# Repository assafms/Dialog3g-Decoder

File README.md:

# Arad Dialog 3G Water Meter Decoder

ESPHome custom component and PCB for reading Arad Dialog 3G water meters using an SI4432 (XL4432) RF module and an ESP8266/ESP32.

## Overview

The Arad Dialog 3G is a water meter deployed in Israel and other countries operating at 916.3 MHz (868 MHz in some regions). This project provides:

- **Custom PCB** connecting an XL4432 module to an ESP via SPI
- **ESPHome component** that receives and decodes meter packets
- **Unified LFSR validation** for all meter groups — single model, no per-group configuration
- **3-bit error correction** — recovers packets with up to 3 corrupted bits
- **ID recovery** — corrects corrupted meter IDs using per-meter constants from validated packets

## Meter Groups

| Group | Bytes 8-9 | Cons Divisor | Notes |
|-------|-----------|-------------|-------|
| Standard | `0x00 0x00` | ÷10 (0.1 m³) | Residential meters |
| Sonata/x40 | `0x00 0x40` | ÷1000 (1 liter) | Commercial/street meters |
| 3D0C | `0x3D 0x0C` | ÷10 (0.1 m³) | Older model |

All groups use the same unified LFSR model with a single universal offset (`0x6FF11521E8`). No per-group detection or configuration needed — bytes 8-9 are just more data bits in the LFSR.

## How It Works

The meter transmits a 21-byte FSK/Manchester-encoded packet every ~30 seconds containing the meter ID and consumption reading. The ESPHome component validates every packet using a unified LFSR-based GF(2) model that works for all meter groups. It also applies up to 3-bit error correction to recover packets with minor RF corruption. Only validated readings are published to Home Assistant.

## Hardware

| Component | Approximate Cost |
|-----------|-----------------|
| ESP8266 or ESP32 | ~$4 |
| XL4432 / SI4432 RF module | ~$2 |
| Custom PCB (see `PCB/`) or manual SPI wiring | ~$0.50 |

See `PCB/` for Eagle source files, Gerber outputs, and board photos.

## RF Parameters

| Parameter | Value |
|-----------|-------|
| Frequency | 916.3 MHz |
| Modulation | FSK |
| Encoding | Manchester (IEEE 802.3) |
| Data Rate | 59.45 kbps |
| Frequency Deviation | 175 kHz |
| Receiver Bandwidth | 600 kHz |
| Transmission Interval | ~30 seconds |
| Preamble | 7 nibbles |
| Sync Word | `0x3E 0x69` |
| Payload | 21 bytes, fixed length, no CRC |

## Quick Start

1. Build the PCB or wire the XL4432 to the ESP via SPI (see `esphome/README.md` for pinout)
2. Copy `esphome/custom_components/xl4432_spi_sensor/` to your ESPHome `custom_components/` directory
3. Add to your YAML:

```yaml
sensor:
  - platform: xl4432_spi_sensor
    name: water_meter
    cs_pin: GPIO15
    meter_id: "0x4E61BC"
    accuracy_decimals: 1
```

4. Find your meter ID: read the decimal serial number on the meter, convert to hex. Example: decimal `5136830` → hex `0x4E61BE`. The packet transmits this big-endian.

## Packet Sniffer Mode

To capture raw packets from all nearby meters:

```yaml
sensor:
  - platform: xl4432_spi_sensor
    name: sniffer
    cs_pin: GPIO15
    meter_id: "0x000000"
    packet_sniff: true
```

All received packets are logged at INFO level. No validation or filtering is performed.

## Wireless Connection

Add `tcp_server: true` to stream packets over WiFi to the Android collector app instead of USB:

```yaml
sensor:
  - platform: xl4432_spi_sensor
    name: sniffer
    cs_pin: GPIO15
    meter_id: "0x000000"
    packet_sniff: true
    tcp_server: true
```

Enable phone hotspot, configure ESPHome WiFi with the hotspot credentials, and the Android app auto-discovers the ESP on port 4321.

## Packet Structure

| Byte(s) | Field | Description |
|---------|-------|-------------|
| 0-1 | Header | Static (`0x0A 0xEC`) |
| 2-4 | Type | Meter type / firmware variant |
| 5-7 | Meter ID | 3 bytes, big-endian |
| 8-9 | Group | `0x00 0x00` standard, `0x00 0x40` x40, `0x3D 0x0C` 3D0C |
| 10-12 | Consumption | 3 bytes, little-endian. STD/3D0C: ÷10 for m³. Sonata/x40: ÷1000 for m³ |
| 13-14 | Status | Usually `0x00 0x05` |
| 15-19 | Scramble | GF(2) integrity field |
| 20 | Trailer | High nibble only (low nibble unreliable due to Manchester timing drift) |

## GF(2) Scrambling Algorithm

Bytes 15-19 of each packet contain a 40-bit value that is a **linear function over GF(2)** of all data bytes 0-14, computed via a single 40-bit LFSR:

```
scrambled = OFFSET ^ ⨁(LFSR_vec[pos] for each set bit in bytes 0-14)
```

Where:
- **OFFSET** = `0x6FF11521E8` — universal, same for all meter groups
- All 120 basis vectors are consecutive states of a 40-bit LFSR (seed `0x51AAF3D980`, 3 feedback taps)
- Forward chain: bytes 12→11→10→9→8→7→6→5→4→3→2→1→0 (104 states)
- Backward chain: bytes 13→14 (16 states, stored as lookup)
- **^** is bitwise XOR

### Validation

Single model for all groups: compute expected scramble via LFSR from bytes 0-14, compare to received bytes 15-19. Up to 3 corrupted bits can be automatically corrected using 160 syndrome bits (120 data + 40 scramble). Achieves 80% STD, 78% x40, 83% 3D0C validation rate. See `PROTOCOL.md` for full details and basis vector tables.

## Links

- [Dialog3g-Decoder-research](https://github.com/assafms/Dialog3g-Decoder-research) — Research repo with analysis scripts, Android collector app, and detailed protocol documentation
- [rtl_433 Protocol 260](https://github.com/merbanan/rtl_433) — SDR-based decoder
- [rtl_433 Issue #1992](https://github.com/merbanan/rtl_433/issues/1992) — Original protocol analysis
- [rtl_433 Discussion #3414](https://github.com/merbanan/rtl_433/discussions/3414) — Arad Sonata analysis

## License

This project is the result of independent reverse engineering for research and interoperability purposes. Not affiliated with Arad Ltd.

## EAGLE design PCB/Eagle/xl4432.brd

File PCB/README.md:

# PCB Design

Custom PCB connecting an XL4432 (SI4432) RF module to an ESP8266/ESP32 via SPI.

## Contents

| Directory | Description |
|-----------|-------------|
| `Eagle/` | Source schematic and board files (Eagle CAD) |
| `Gerber/` | Production-ready Gerber files (PCBWay compatible) |

## Assembly Notes

- **R1, R2, R3**: Use 0-ohm resistors or solder bridges (short the pads)
- See `schematic.png` and `pcb.png` for reference
- `completed board.png` shows an assembled example

## Bill of Materials

See `Eagle/BOM` for the full component list.

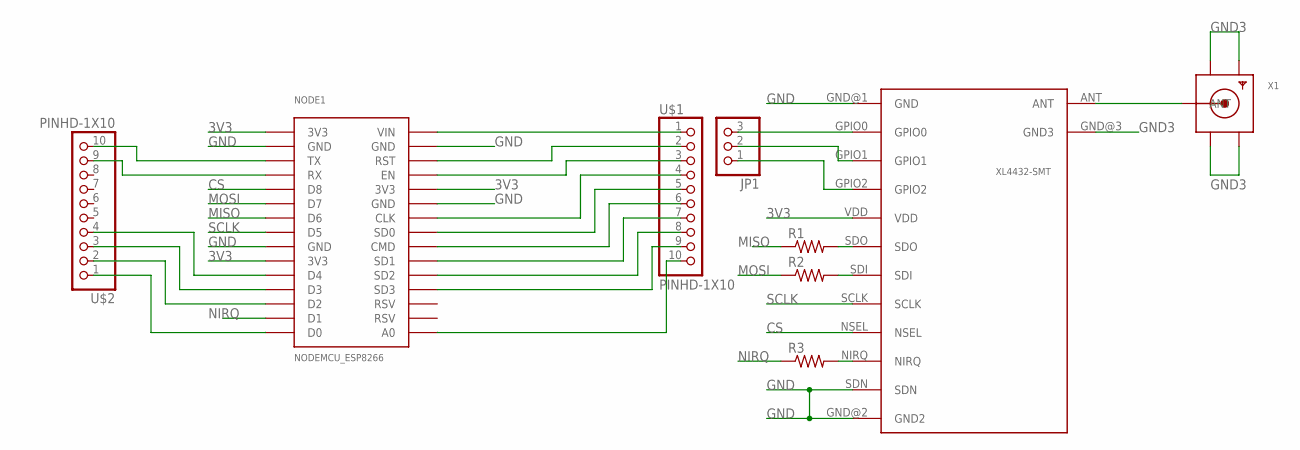
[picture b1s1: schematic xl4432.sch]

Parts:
4332-1: XM4432-SMT; XL4432-SMT
JP1: PINHD-1X3; 1X03
NODE1: NODEMCU_ESP8266
R1, R2, R3: R-US_R2012; R2012
U$1, U$2: PINHD-1X10; 1X10-BIG
X1: SMACONNECTOR; SMA90_DIP

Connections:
3V3: 4332-1.VDD, NODE1.3V3@1 (3V3), NODE1.3V3@2 (3V3), NODE1.3V3@3 (3V3)
CS: 4332-1.NSEL, NODE1.D8
GND: 4332-1.GND@1 (GND), 4332-1.GND@2 (GND2), 4332-1.SDN, NODE1.GND@1 (GND), NODE1.GND@2 (GND), NODE1.GND@3 (GND), NODE1.GND@4 (GND)
GND3: 4332-1.GND@3 (GND3), X1.GND1, X1.GND2, X1.GND3, X1.GND4
MISO: NODE1.D6, R1.1
MOSI: NODE1.D7, R2.1
unnamed: 4332-1.ANT, X1.ANTENNA (ANT)
unnamed: 4332-1.GPIO0, JP1.3
unnamed: 4332-1.GPIO1, JP1.2
unnamed: 4332-1.GPIO2, JP1.1
unnamed: NODE1.VIN, U$1.1
unnamed: NODE1.RST, U$1.2
unnamed: NODE1.EN, U$1.3
unnamed: NODE1.CLK, U$1.4
unnamed: NODE1.SDO (SD0), U$1.5
unnamed: NODE1.CMD, U$1.6
unnamed: NODE1.SD1, U$1.7
unnamed: NODE1.SD2, U$1.8
unnamed: NODE1.SD3, U$1.9
unnamed: NODE1.A0, U$1.10
unnamed: NODE1.TX, U$2.10
unnamed: NODE1.RX, U$2.9
unnamed: NODE1.D0, U$2.1
unnamed: NODE1.D2, U$2.2
unnamed: NODE1.D3, U$2.3
unnamed: NODE1.D4, U$2.4
unnamed: 4332-1.SDO, R1.2
unnamed: 4332-1.SDI, R2.2
unnamed: 4332-1.NIRQ, R3.2
NIRQ: NODE1.D1, R3.1
SCLK: 4332-1.SCLK, NODE1.D5

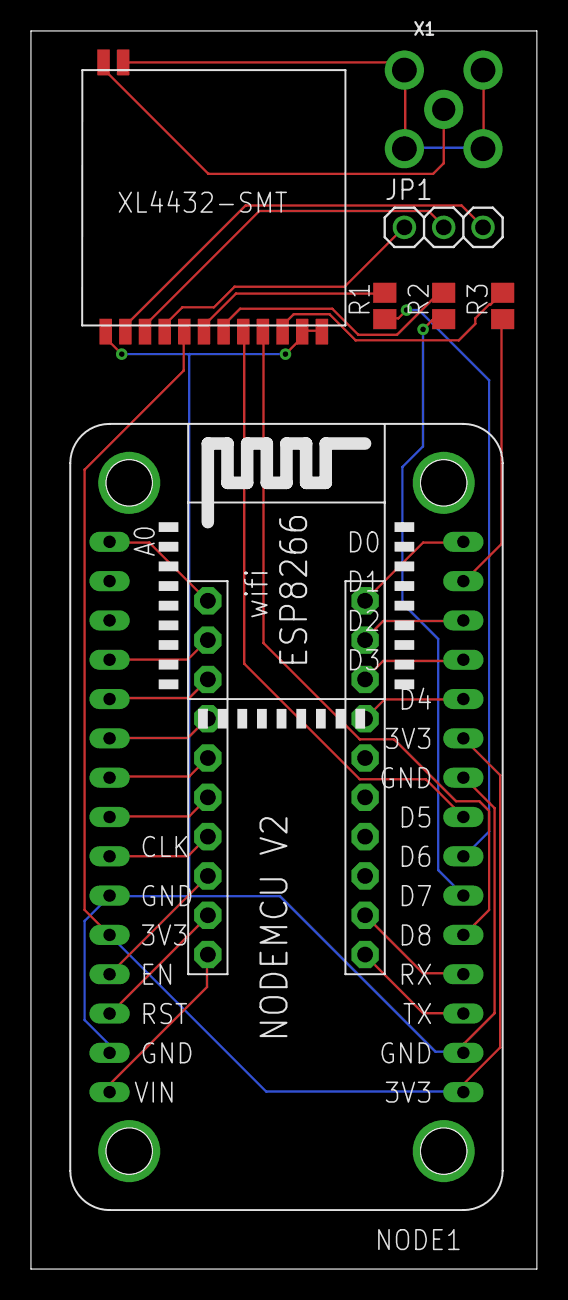
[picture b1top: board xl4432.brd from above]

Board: 2 copper layers, 32.7 x 80.0 mm, 9 parts (0 on the bottom side), 31 nets.

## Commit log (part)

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2023-08-28 Initial commit
    Initial commit
2025-06-18 Debug and Raw sniffing
    Added the ability to sniff any meter id .
    Added Syslog
    Better check for the packet to prevent errors as we dont have a CRC
2025-06-18 Fix readme
2025-06-24 Moved meter_id to yaml
    Moved the setting of the meter_id from the code to the yaml. as always , if the meter_id is not what you set , you can see the raw packet in the log and see the meter_id
2026-03-28 Validator
2026-03-28 Added 3bit correction

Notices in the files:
parts and their libraries:
xl4432-smt: Drawn by Will Cooke.  Made available under the GPL.  For full licence details please see the github page or read any copy of the GPL v2.
